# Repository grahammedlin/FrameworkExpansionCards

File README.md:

View this project on [CADLAB.io](https://cadlab.io/project/26746). 

# FrameworkExpansionCards

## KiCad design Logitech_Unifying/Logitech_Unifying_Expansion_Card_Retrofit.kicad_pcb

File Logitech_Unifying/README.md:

# Logitech Unifying Reciever Adapter

Some Logitech mice still require a proprietary USB-A dongle. 
Ripping off the enclosure, the USB contacts are on the PCB.
This is a simple adapter with castellated holes to hide the recievers inside a Framework Expansion Card.

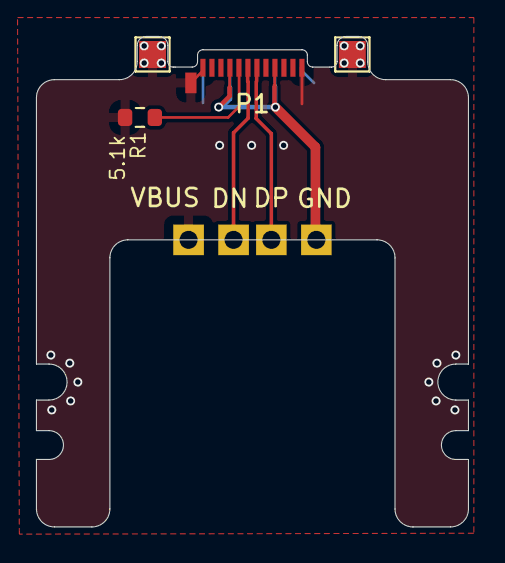
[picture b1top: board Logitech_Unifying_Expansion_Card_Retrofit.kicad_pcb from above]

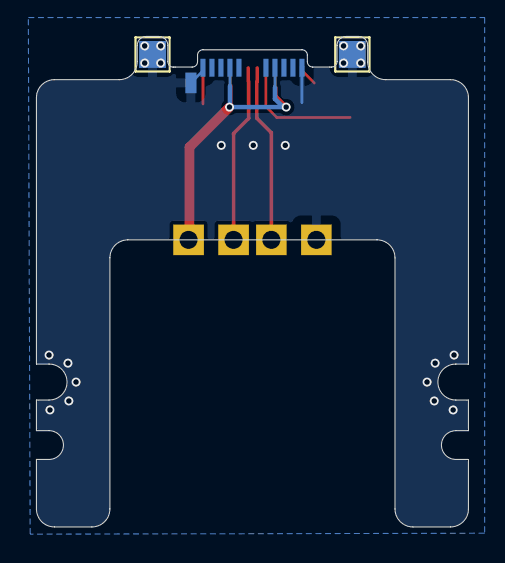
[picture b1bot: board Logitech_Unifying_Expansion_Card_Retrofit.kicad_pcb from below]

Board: 2 copper layers, 24.0 x 27.3 mm, 10 parts (2 on the bottom side), 5 nets.

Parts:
DN: Castellated_2
DP: Castellated_2
GND: Castellated_2
P1: USB_C_Plug_USB2.0; USB_C_Plug_Molex_105444_0.2mm_Spacing
R1: 5.1k; R_0603_1608Metric
TP1, TP2, TP3, TP4: TestPoint; TestPoint_Pad_1.5x1.5mm
VBUS: Castellated_2

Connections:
/USB_DN: DP.1, P1.A7 (D-)
/USB_DP: DN.1, P1.A6 (D+)
GND: P1.A1 (GND), P1.A12 (GND), P1.B1 (GND), P1.B12 (GND), P1.S1 (SHIELD), R1.2, TP1.1, TP2.1, TP3.1, TP4.1, VBUS.1
unnamed: P1.A5 (CC), R1.1
VBUS: GND.1, P1.A4 (VBUS), P1.A9 (VBUS), P1.B4 (VBUS), P1.B9 (VBUS)

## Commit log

2023-04-06 init
2023-04-07 Readme
2023-04-07 Backlink to CADLAB.io has been added.
2023-04-07 small revision for cadlab test
2023-04-07 small change to test cadlab
2023-04-13 flipped USB-C relative to reciever
2023-04-13 increase USB-C mask bridge width for manufacture

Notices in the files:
Logitech_Unifying/Logitech_Unifying_Expansion_Card_Retrofit.kicad_pcb:
This work is licensed under a Creative Commons Attribution 4.0 International License
